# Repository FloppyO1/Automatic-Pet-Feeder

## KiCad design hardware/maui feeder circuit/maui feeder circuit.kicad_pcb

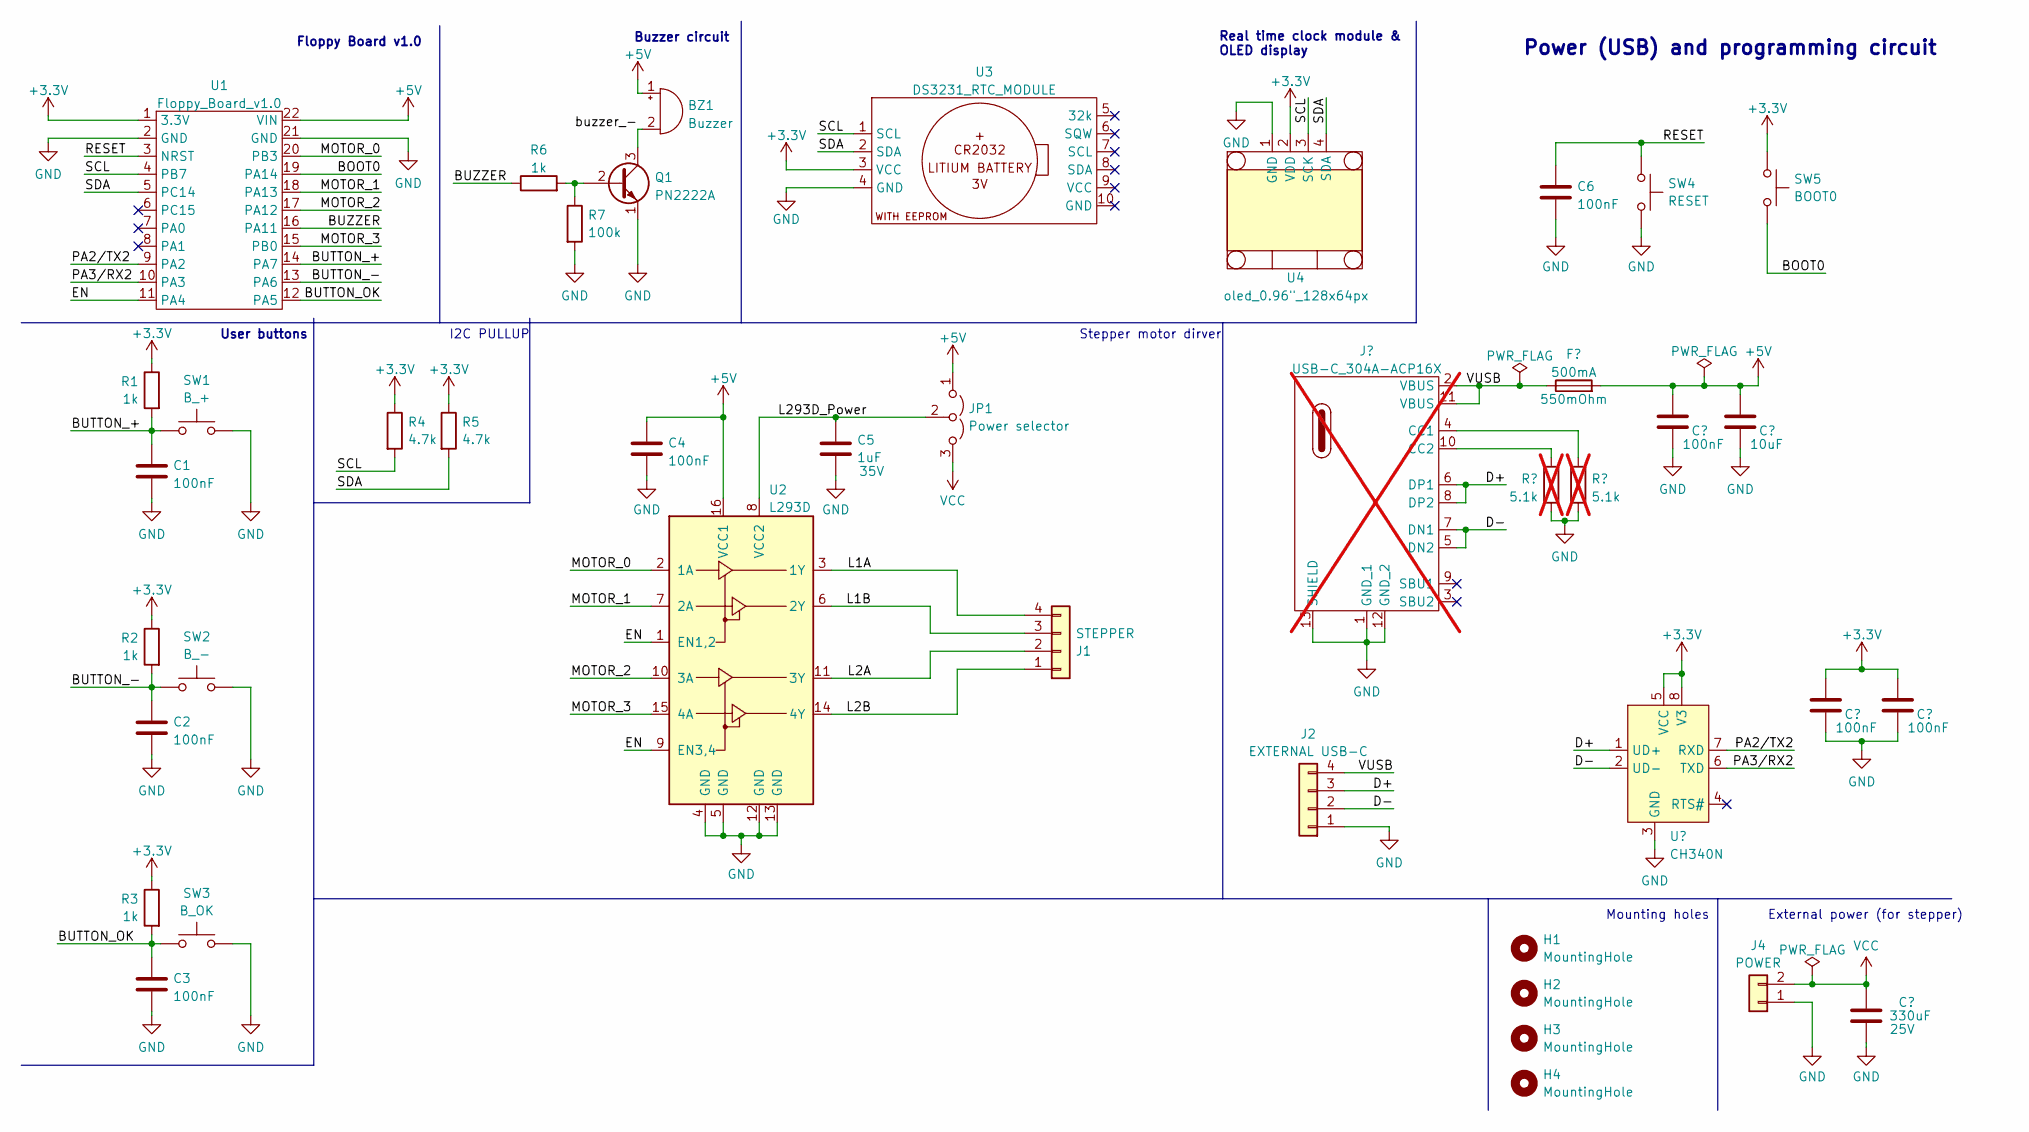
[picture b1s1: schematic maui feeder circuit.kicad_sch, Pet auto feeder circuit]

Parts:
BZ1: Buzzer; MagneticBuzzer_PUI_AT-0927-TT-6-R
C1, C2, C3, C4, C6, C7, C9, C11: 100nF; C_0603_1608Metric
C5: 1uF; C_0603_1608Metric; Voltage 35V
C8: 10uF; C_0603_1608Metric
C10: 330uF; CP_Elec_6.3x7.7; Voltage 25V
F1: 500mA; Fuse_1206_3216Metric_Pad1.42x1.75mm_HandSolder
H1, H2, H3, H4: MountingHole; MountingHole_3.2mm_M3_Pad
J1: STEPPER; JST_XH_B4B-XH-A_1x04_P2.50mm_Vertical
J2: EXTERNAL USB-C; JST_XH_B4B-XH-A_1x04_P2.50mm_Vertical
J3: USB-C_304A-ACP16X; USB_C_304A-ACP16X; not fitted
J4: POWER; JST_XH_B2B-XH-A_1x02_P2.50mm_Vertical
JP1: Power selector; SolderJumper-3_P1.3mm_Open_RoundedPad1.0x1.5mm
Q1: PN2222A; TO-92_Inline
R1, R2, R3, R6: 1k; R_0603_1608Metric
R4, R5: 4.7k; R_0603_1608Metric
R7: 100k; R_0603_1608Metric
R8, R9: 5.1k; R_0603_1608Metric; not fitted
SW1: B_+; SMD BUTTON 5.1x5.1
SW2: B_-; SMD BUTTON 5.1x5.1
SW3: B_OK; SMD BUTTON 5.1x5.1
SW4: RESET; SW_Tactile_SPST_NO_Straight_CK_PTS636Sx25SMTRLFS
SW5: BOOT0; SW_Tactile_SPST_NO_Straight_CK_PTS636Sx25SMTRLFS
U1: Floppy_Board_v1.0; Floppy board v1.0
U2: L293D; DIP-16_W7.62mm
U3: DS3231_RTC_MODULE; JST_XH_B4B-XH-A_1x04_P2.50mm_Vertical
U4: oled_0.96"_128x64px; 128x64OLED
U5: CH340N; SOP-8_3.9x4.9mm_P1.27mm

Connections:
+3.3V: C9.1, C11.1, R1.1, R2.1, R3.1, R4.1, R5.1, SW5.1, U1.1 (3.3V), U3.3 (VCC), U4.2 (VDD), U5.5 (VCC), U5.8 (V3)
+5V: BZ1.1 (-), C4.1, C7.1, C8.1, F1.2, JP1.1 (A), U1.22 (VIN), U2.16 (VCC1)
/BOOT0: SW5.2, U1.19 (PA14)
/BUTTON_+: C1.1, R1.2, SW1.1, U1.14 (PA7)
/BUTTON_-: C2.1, R2.2, SW2.1, U1.13 (PA6)
/BUTTON_OK: C3.1, R3.2, SW3.1, U1.12 (PA5)
/BUZZER: R6.1, U1.16 (PA11)
/D+: J2.3, J3.6 (DP1), J3.8 (DP2), U5.1 (UD+)
/D-: J2.2, J3.5 (DN2), J3.7 (DN1), U5.2 (UD-)
/EN: U1.11 (PA4), U2.1 (EN1,2), U2.9 (EN3,4)
/L1A: J1.4, U2.3 (1Y)
/L1B: J1.3, U2.6 (2Y)
/L2A: J1.2, U2.11 (3Y)
/L2B: J1.1, U2.14 (4Y)
/L293D_Power: C5.1, JP1.2 (C), U2.8 (VCC2)
/MOTOR_0: U1.20 (PB3), U2.2 (1A)
/MOTOR_1: U1.18 (PA13), U2.7 (2A)
/MOTOR_2: U1.17 (PA12), U2.10 (3A)
/MOTOR_3: U1.15 (PB0), U2.15 (4A)
/PA2/TX2: U1.9 (PA2), U5.7 (RXD)
/PA3/RX2: U1.10 (PA3), U5.6 (TXD)
/RESET: C6.1, SW4.1, U1.3 (NRST)
/SCL: R4.2, U1.4 (PB7), U3.1 (SCL), U4.3 (SCK)
/SDA: R5.2, U1.5 (PC14), U3.2 (SDA), U4.4 (SDA)
/VUSB: F1.1, J2.4, J3.2 (VBUS), J3.11 (VBUS)
/buzzer_-: BZ1.2 (+), Q1.3 (C)
GND: C1.2, C2.2, C3.2, C4.2, C5.2, C6.2, C7.2, C8.2, C9.2, C10.2, C11.2, J2.1, J3.1 (GND_1), J3.12 (GND_2), J3.13 (SHIELD), J4.1, Q1.1 (E), R7.2, R8.1, R9.2, SW1.2, SW2.2, SW3.2, SW4.2, U1.2 (GND), U1.21 (GND), U2.4 (GND), U2.5 (GND), U2.12 (GND), U2.13 (GND), U3.4 (GND), U4.1 (GND), U5.3 (GND)
unnamed: J3.4 (CC1), R9.1
unnamed: J3.10 (CC2), R8.2
unnamed: Q1.2 (B), R6.2, R7.1
VCC: C10.1, J4.2, JP1.3 (B)

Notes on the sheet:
External power (for stepper)
Stepper motor dirver
Real time clock module & OLED display
Buzzer circuit
Power (USB) and programming circuit
I2C PULLUP
Floppy Board v1.0
User buttons
Mounting holes

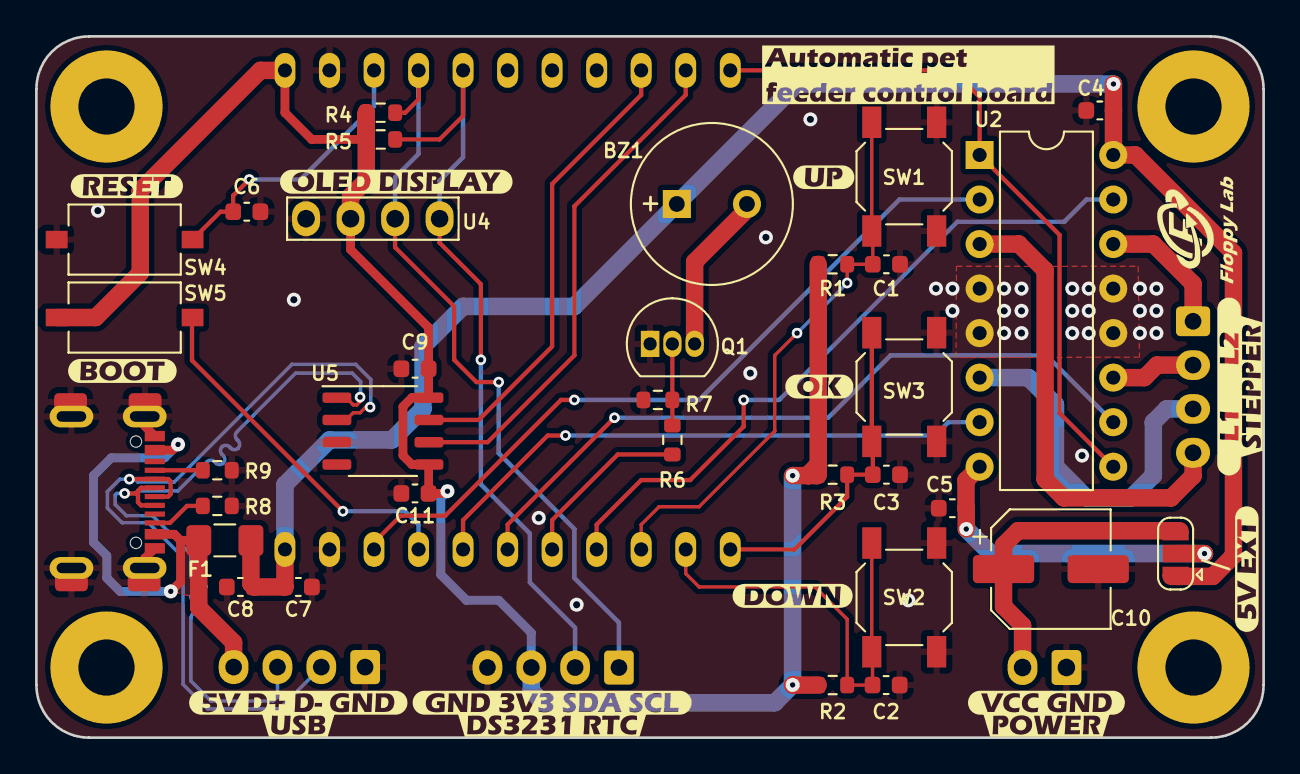
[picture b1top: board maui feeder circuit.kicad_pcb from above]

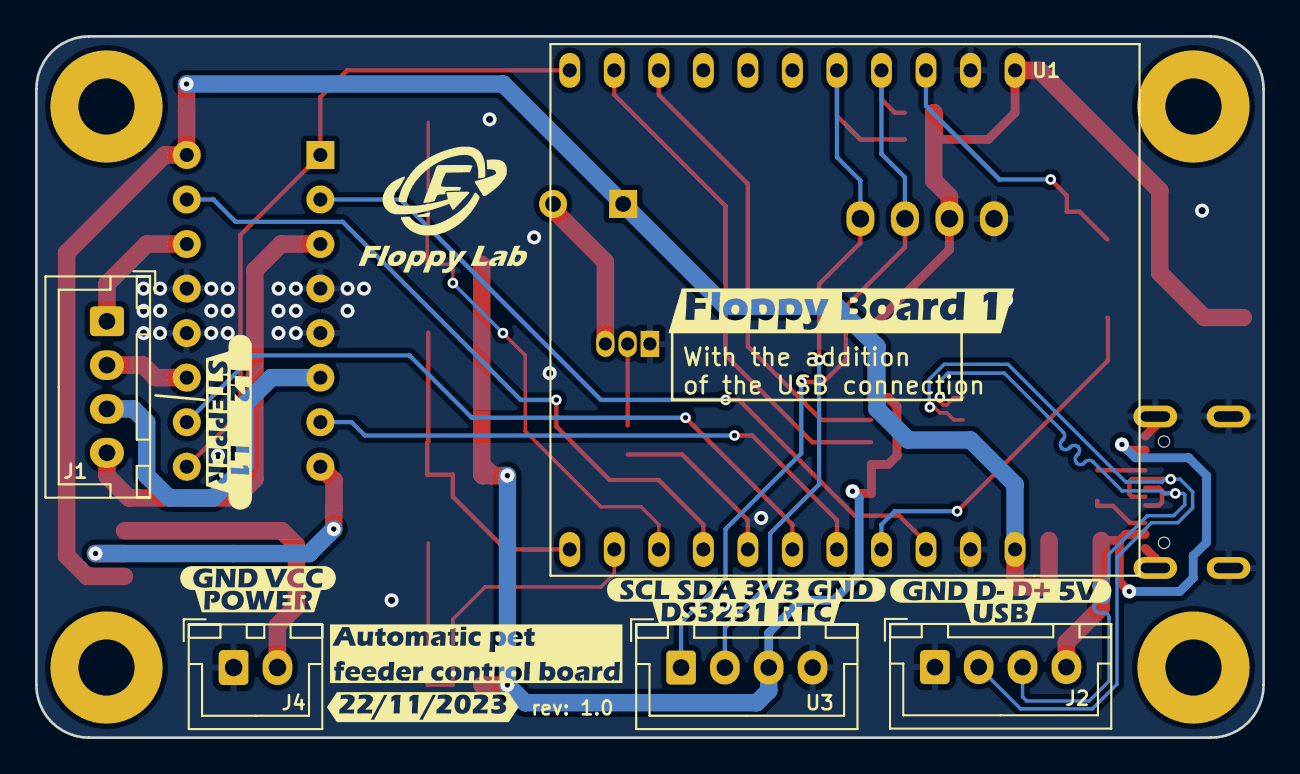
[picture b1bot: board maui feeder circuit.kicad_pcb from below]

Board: 2 copper layers, 70.0 x 40.0 mm, 69 parts (16 on the bottom side), 31 nets.

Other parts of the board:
kibuzzard-655E5A8C, kibuzzard-655E5A8C#2: G***; kibuzzard-655E5A8C
kibuzzard-655E5A9C: G***; kibuzzard-655E5A9C
kibuzzard-655E5ABC: G***; kibuzzard-655E5ABC
kibuzzard-655E5B7A: G***; kibuzzard-655E5B7A
kibuzzard-655E5B48: G***; kibuzzard-655E5B48
kibuzzard-655E5B52, kibuzzard-655E5B52#2: G***; kibuzzard-655E5B52
kibuzzard-655E5B87: G***; kibuzzard-655E5B87
kibuzzard-655E5B91: G***; kibuzzard-655E5B91
kibuzzard-655E5BB9: G***; kibuzzard-655E5BB9
kibuzzard-655E5BC2: G***; kibuzzard-655E5BC2
kibuzzard-655E6B51: G***; kibuzzard-655E6B51
kibuzzard-655E6C3A, kibuzzard-655E6C3A#2: G***; kibuzzard-655E6C3A
kibuzzard-655E6C5E: G***; kibuzzard-655E6C5E
kibuzzard-655E6CD0: G***; kibuzzard-655E6CD0
kibuzzard-655E6CF0: G***; kibuzzard-655E6CF0
kibuzzard-655E6D66: G***; kibuzzard-655E6D66
kibuzzard-655E6DEF: G***; kibuzzard-655E6DEF
kibuzzard-655E59BB, kibuzzard-655E59BB#2: G***; kibuzzard-655E59BB
kibuzzard-655E59DB, kibuzzard-655E59DB#2: G***; kibuzzard-655E59DB
kibuzzard-655E59EA: G***; kibuzzard-655E59EA
kibuzzard-655E71CE: G***; kibuzzard-655E71CE
kibuzzard-655E598F: G***; kibuzzard-655E598F

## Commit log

2024-02-22 added all the files
2024-03-27 pet feeder stm32ide project
